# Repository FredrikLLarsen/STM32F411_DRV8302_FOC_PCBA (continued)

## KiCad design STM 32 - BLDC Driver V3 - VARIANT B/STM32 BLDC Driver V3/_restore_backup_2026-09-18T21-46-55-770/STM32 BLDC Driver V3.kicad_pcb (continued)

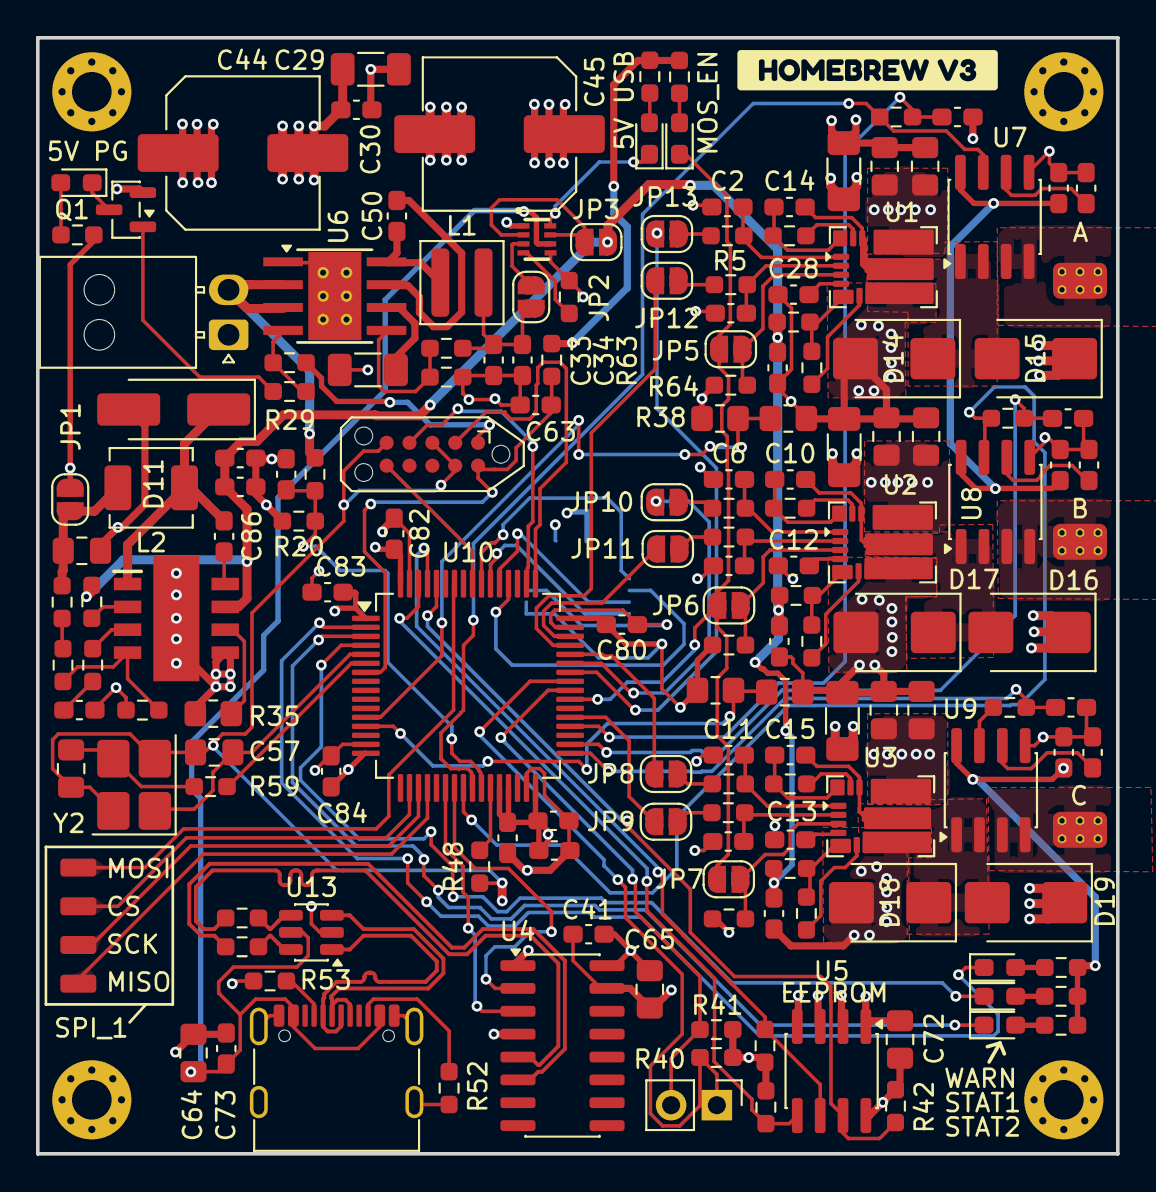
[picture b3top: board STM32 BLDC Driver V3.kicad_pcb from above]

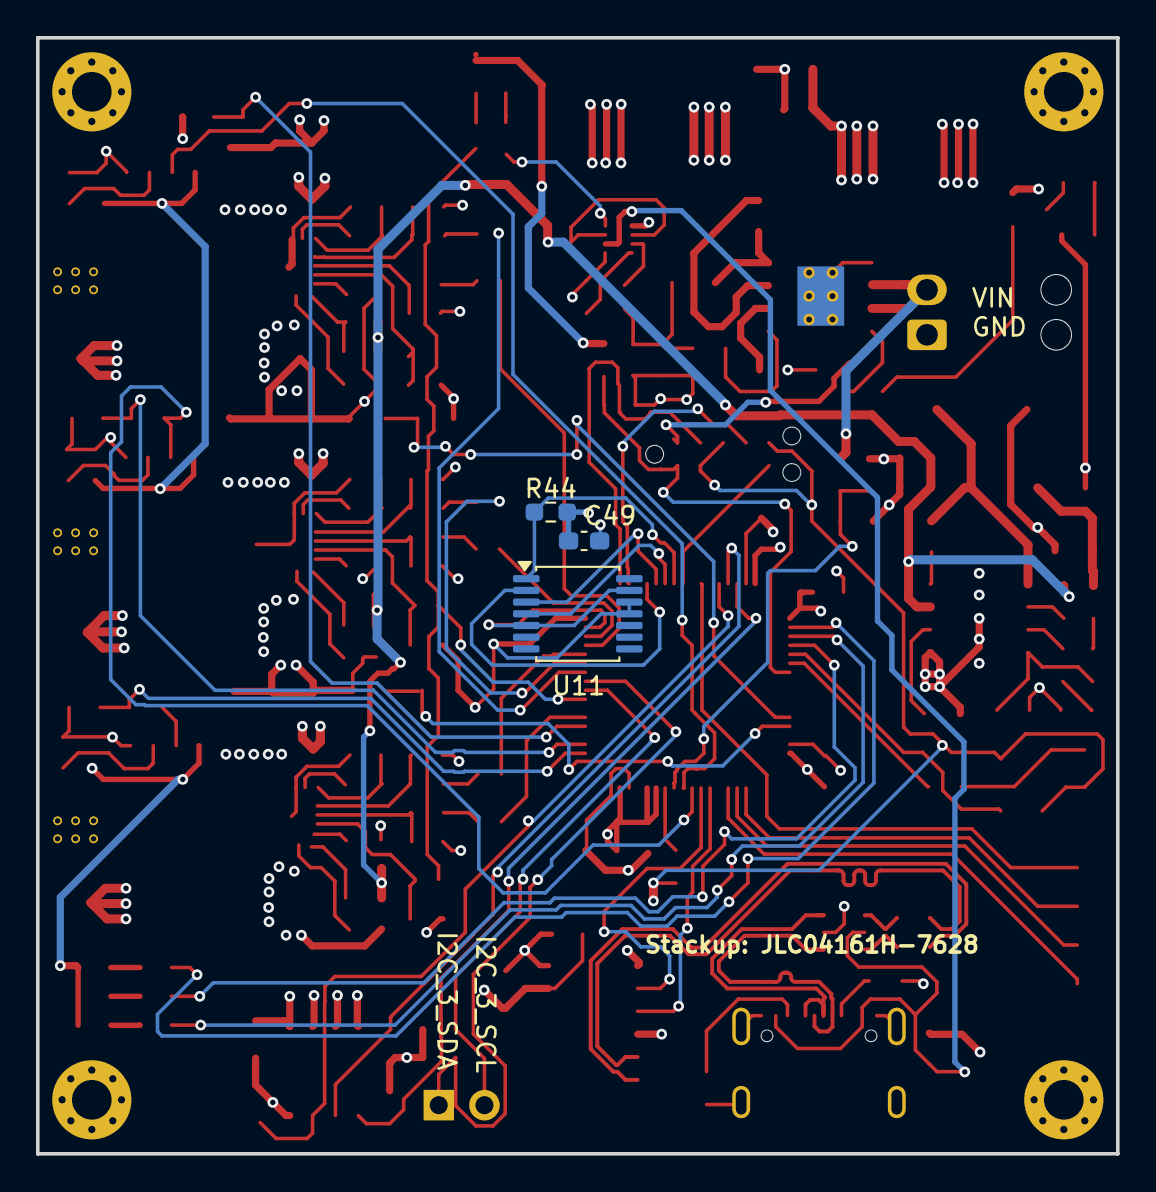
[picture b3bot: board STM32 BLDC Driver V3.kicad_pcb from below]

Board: 4 copper layers, 60.0 x 62.0 mm, 180 parts (3 on the bottom side), 122 nets.

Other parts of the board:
kobee-studio-6AB1898F: Kobee Studio; kobee-studio-6AB1898F

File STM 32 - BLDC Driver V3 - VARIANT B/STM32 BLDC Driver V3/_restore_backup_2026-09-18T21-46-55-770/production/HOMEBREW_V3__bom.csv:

Designator,Footprint,Quantity,Value,LCSC Part #
"C10, C12, C13, C14, C15, C25, C26, C28, C32, C37",0603,10,2.2uF (C57895),
"C11, C2, C5, C6, C7, C9",0603,6,22pF (C7419421),
"C19, C22, C31, C38",1206,4,1uf 100V (C13832),
C27,0603,1,22nF (C696861),
C29,1206,1,4.7uF 100V (C22367839),
C30,0603,1,220nF 100V (C7300906),
"C33, C34",0603,2,22uF 10V (C86295),
"C35, C36, C41",0603,3,10uF 10V (C5137565),
C39,0805,1,47uF 10V (C124129),
"C43, C47, C48, C49, C50",0603,5,0.1uF (C52711259),
"C44, C45",C_Elec_8x10.2,2,100uF 63V (C7471891),
"C57, C58",0805,2,10pF (C520053),
"C62, C63, C80, C82, C83, C84, C85, C86",0603,8,100nF 50V (C1591),
"C64, C65, C72",0805,3,100nF 50V (C28233),
"C66, C67, C68, C69, C70, C71",0805,6,100nF 100V X7R,
C73,0603,1,4.7uF 16V (C7432772),
"C74, C75, C76, C77, C78, C79, C81",0603,7,1nF (C374073),
"D10, D12, D13, D7, D8, D9",0603,6,C5342734,
D11,D_SMA_Handsoldering,1,B340A,
"D14, D15, D16, D17, D18, D19",D_SMB,6,C28646299,
IC1,SOIC127P600X170-9N,1,MP1584EN-LF-Z,
IC2,SOT8,1,LM66200DRLR,
J1,PinHeader_1x02_P2.54mm_Vertical,1,Conn_01x02_Pin,
"J11, J5, J7, J8",STICHED SOLDER PAD_SMALL,4,Conn_01x01_Pin,
J12,USB_C_Receptacle_G-Switch_GT-USB-7010ASV,1,G-Switch GT-USB-7010ASV,
"J2, J3, J4",STICHED SOLDER PAD,3,Conn_01x01_Pin,
J9,Molex_Nano-Fit_105313-xx02_1x02_P2.50mm_Horizontal,1,Conn_01x02_Pin,
"JP1, JP10, JP11, JP12, JP13, JP2, JP3, JP5, JP6, JP7, JP8, JP9",SolderJumper-2_P1.3mm_Open_RoundedPad1.0x1.5mm,12,Jumper_2_Small_Open,
L1,L_Abracon_ASPIAIG-F4020,1,10 µH (C54620135),
L2,L_Sunlord_MWSA0402S,1,22uH (C41438718),
Q1,SOT-23,1,BC847,
"R13, R14, R16, R17, R18, R19",0603,6,10R 0.1W (C109318),
"R2, R4, R5, R6, R7, R8",0603,6,2.2R (C2907006),
R20,0603,1,4.3k 1% (C54920924),
"R21, R23, R40, R41, R42, R44, R51, R57, R58",0603,9,4k7 100mW (C2907034),
"R22, R24, R25, R28, R30, R39, R45",0603,7,820R (C137608),
"R26, R29, R32, R34, R43",0603,5,100k 1% (C2906980),
R27,0603,1,24.9k 1% (C2930080),
R33,0603,1,68k (C2907063),
R35,0805,1,250k (C2501409),
R36,0603,1,22k (C2907015),
"R37, R38",0805,2,8.2k (C17828),
"R46, R47",0603,2,22R (C23345),
"R48, R59, R60, R62, R68",0603,5,0R (C2906974),
"R52, R53",0603,2,5.1k (C2907044),
"R55, R63, R64, R65, R66, R67",0603,6,10k 100mW (C98220),
"TH2, TH3",0805,2,CMFB103F3950FANT (C51597),
"U1, U2, U3",EPC_QFN-13-3EP_3.5x5mm_P0.5mm,3,EPC23104,
U10,LQFP-64_10x10mm_P0.5mm,1,STM32G431RBTx,
U11,TSSOP-14_4.4x5mm_P0.65mm,1,AS5047D,
U13,SOT-23-6,1,USBLC6-2SC6,
U4,SOIC-16_3.9x9.9mm_P1.27mm,1,CH340C,
U5,SOIC-8_3.9x4.9mm_P1.27mm,1,24LC256,
U6,Texas_HTSOP-8-1EP_3.9x4.9mm_P1.27mm_EP2.95x4.9mm_Mask2.4x3.1mm_ThermalVias,1,LMR36520ADDA,
"U7, U8, U9",SOIC-8_3.9x4.9mm_P1.27mm,3,ACS725xLCTR-20AB,
Y2,Crystal_SMD_3225-4Pin_3.2x2.5mm_HandSoldering,1,Crystal_GND24 (C5444547),

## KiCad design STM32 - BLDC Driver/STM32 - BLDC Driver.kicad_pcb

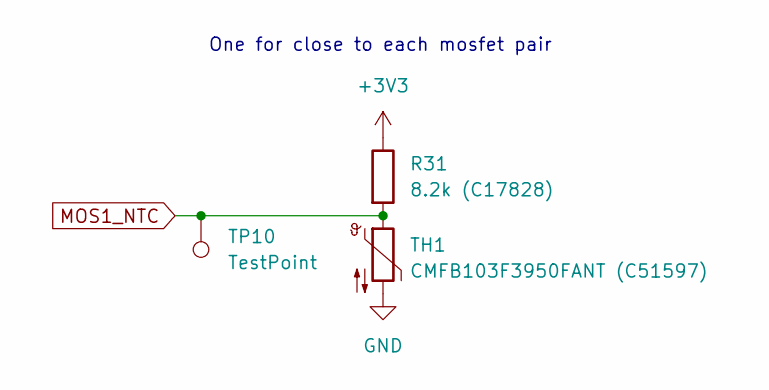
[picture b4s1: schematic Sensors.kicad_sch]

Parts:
R31: 8.2k (C17828); R_0805_2012Metric_Pad1.20x1.40mm_HandSolder
TH1: CMFB103F3950FANT (C51597); R_0805_2012Metric_Pad1.20x1.40mm_HandSolder
TP10: TestPoint; TestPoint_Pad_D3.0mm

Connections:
+3V3: R31.1; also elsewhere on the board
GND: TH1.2; also elsewhere on the board
MOS1_NTC: R31.2, TH1.1, TP10.1; also elsewhere on the board

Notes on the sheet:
One for close to each mosfet pair

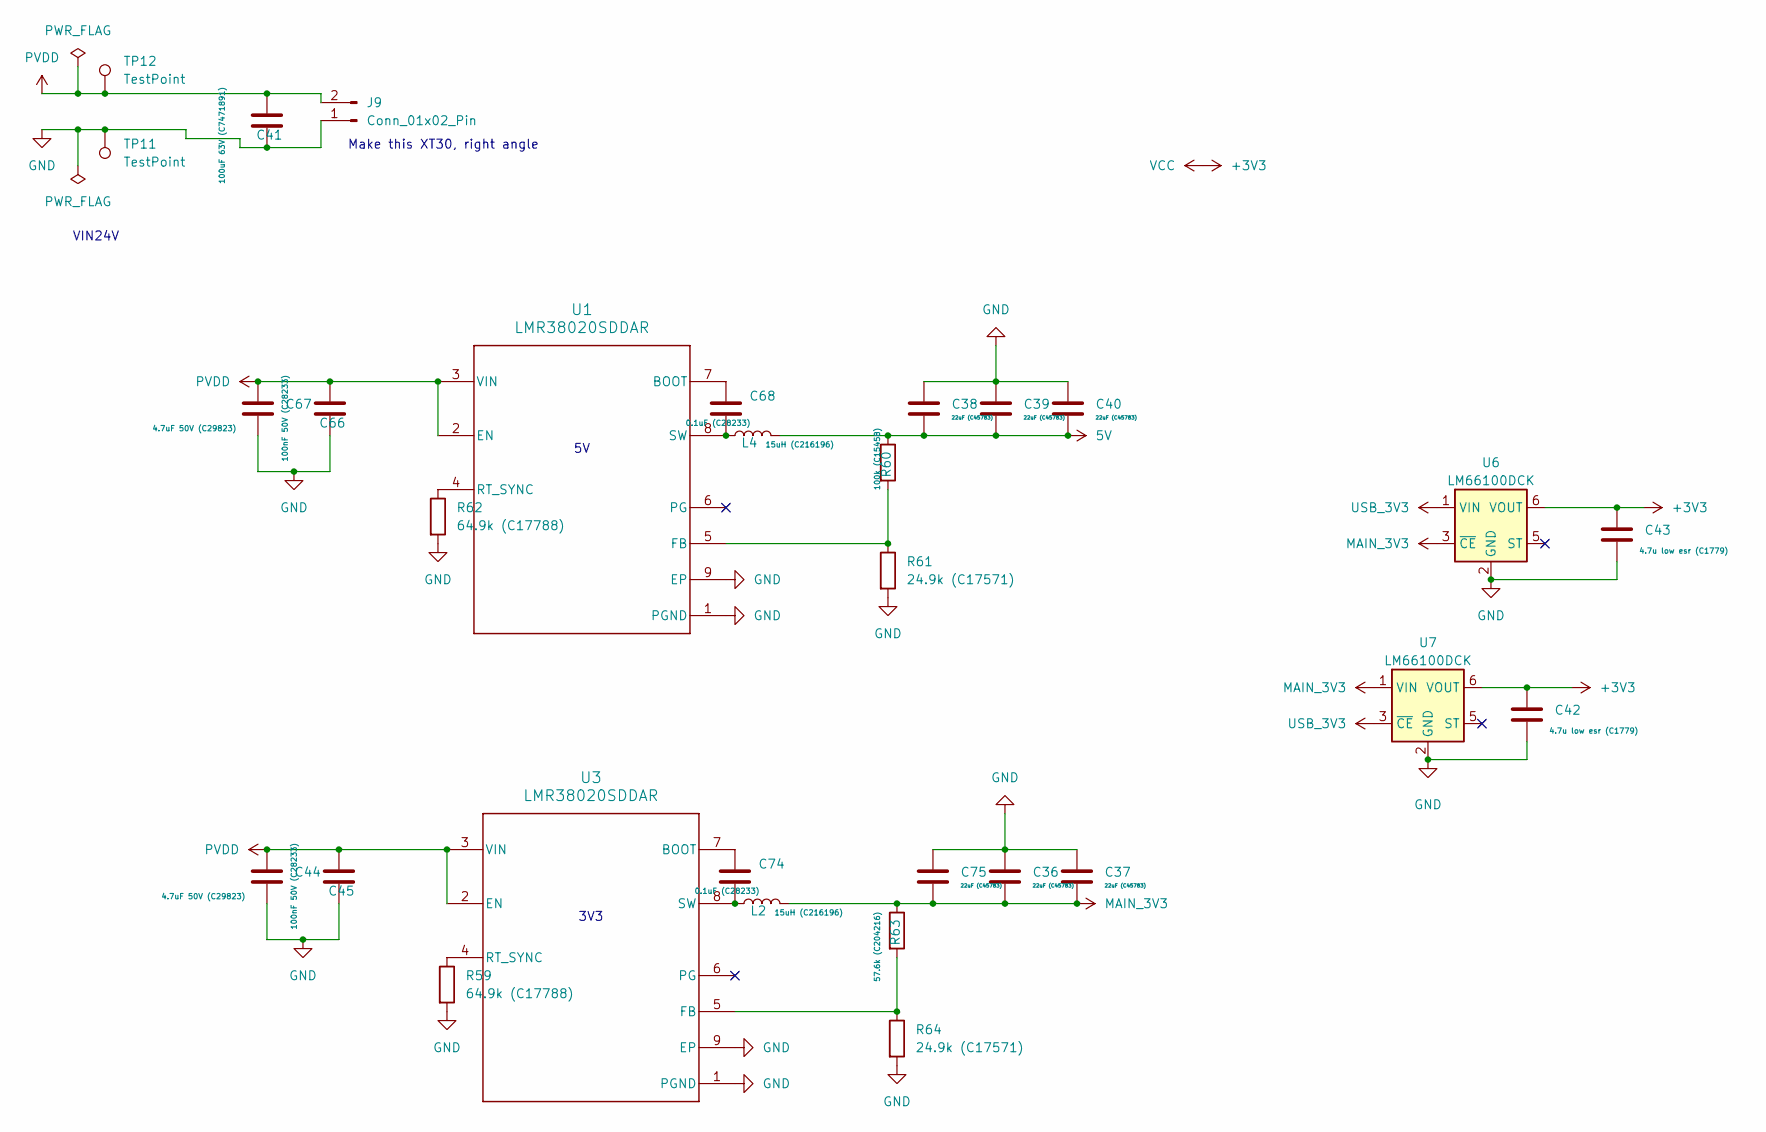
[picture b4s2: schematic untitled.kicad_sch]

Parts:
C36, C37, C38, C39, C40, C75: 22uF (C45783); C_0805_2012Metric_Pad1.18x1.45mm_HandSolder
C41: 100uF 63V (C7471891); C_Elec_8x10.2
C42, C43: 4.7u low esr (C1779); C_0805_2012Metric_Pad1.18x1.45mm_HandSolder
C44, C67: 4.7uF 50V (C29823); C_1206_3216Metric_Pad1.33x1.80mm_HandSolder
C45, C66: 100nF 50V (C28233); C_0805_2012Metric_Pad1.18x1.45mm_HandSolder
C68, C74: 0.1uF (C28233); C_0805_2012Metric_Pad1.18x1.45mm_HandSolder
J9: Conn_01x02_Pin; AMASS_XT30PW-M_1x02_P2.50mm_Horizontal
L2, L4: 15uH (C216196); L_7.3x7.3_H3.5
R59, R62: 64.9k (C17788); R_0805_2012Metric_Pad1.20x1.40mm_HandSolder
R60: 100k (C15458); R_0603_1608Metric_Pad0.98x0.95mm_HandSolder
R61, R64: 24.9k (C17571); R_0805_2012Metric_Pad1.20x1.40mm_HandSolder
R63: 57.6k (C204216); R_0603_1608Metric_Pad0.98x0.95mm_HandSolder
TP11, TP12: TestPoint; TestPoint_Pad_D4.0mm
U1, U3: LMR38020SDDAR; DDA0008E-IPC_A
U6, U7: LM66100DCK; SOT-363_SC-70-6

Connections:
5V: C38.2, C39.2, C40.2, L4.2, R60.1; also elsewhere on the board
+3V3: C42.1, C43.1, U6.6 (VOUT), U7.6 (VOUT); also elsewhere on the board
GND: C36.1, C37.1, C38.1, C39.1, C40.1, C41.1, C42.2, C43.2, C44.2, C45.1, C66.1, C67.2, C75.1, J9.1, R59.2, R61.2, R62.2, R64.2, TP11.1, U1.1 (PGND), U1.9 (EP), U3.1 (PGND), U3.9 (EP), U6.2 (GND), U7.2 (GND); also elsewhere on the board
MAIN_3V3: C36.2, C37.2, C75.2, L2.2, R63.1, U6.3 (~CE), U7.1 (VIN)
unnamed: C68.1, U1.7 (BOOT)
unnamed: R60.2, R61.1, U1.5 (FB)
unnamed: R62.1, U1.4 (RT_SYNC)
unnamed: C68.2, L4.1, U1.8 (SW)
unnamed: C74.1, U3.7 (BOOT)
unnamed: R63.2, R64.1, U3.5 (FB)
unnamed: R59.1, U3.4 (RT_SYNC)
unnamed: C74.2, L2.1, U3.8 (SW)
PVDD: C41.2, C44.1, C45.2, C66.2, C67.1, J9.2, TP12.1, U1.2 (EN), U1.3 (VIN), U3.2 (EN), U3.3 (VIN); also elsewhere on the board
USB_3V3: U6.1 (VIN), U7.3 (~CE); also elsewhere on the board

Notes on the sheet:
Make this XT30, right angle
3V3
VIN24V

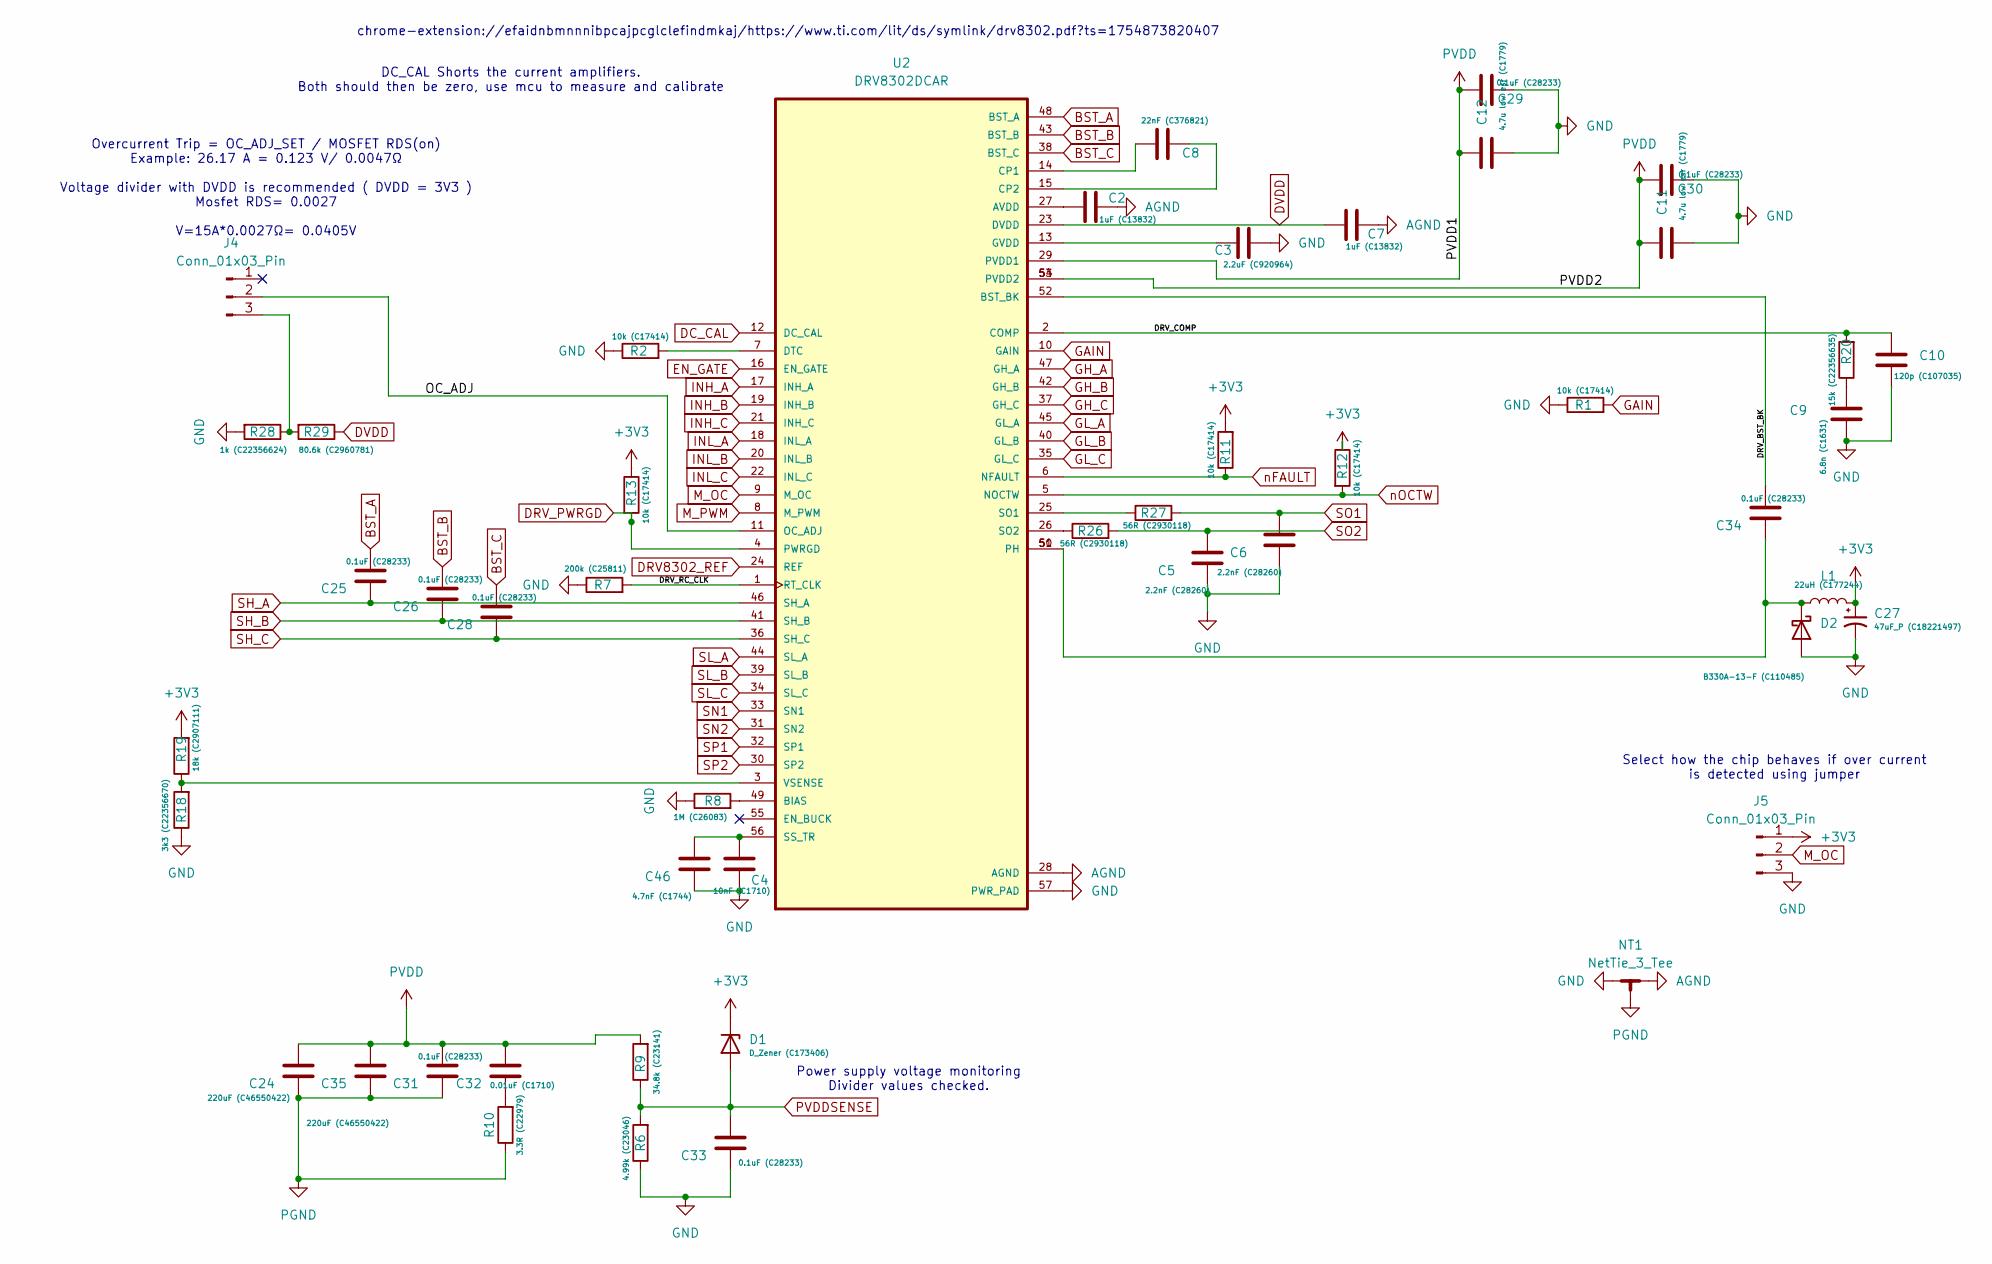
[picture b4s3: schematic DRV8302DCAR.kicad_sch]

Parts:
C2, C7: 1uF (C13832); C_1206_3216Metric_Pad1.33x1.80mm_HandSolder
C3: 2.2uF (C920964); C_1206_3216Metric_Pad1.33x1.80mm_HandSolder
C4: 10nF (C1710); C_0805_2012Metric_Pad1.18x1.45mm_HandSolder
C5, C6: 2.2nF (C28260); C_0805_2012Metric_Pad1.18x1.45mm_HandSolder
C8: 22nF (C376821); C_0603_1608Metric_Pad1.08x0.95mm_HandSolder
C9: 6.8n (C1631); C_0603_1608Metric_Pad1.08x0.95mm_HandSolder
C10: 120p (C107035); C_0603_1608Metric_Pad1.08x0.95mm_HandSolder
C11, C12: 4.7u low esr (C1779); C_0805_2012Metric_Pad1.18x1.45mm_HandSolder
C24, C35: 220uF (C46550422); C_Elec_10x10.2
C25, C26, C28, C29, C30, C31, C33, C34: 0.1uF (C28233); C_0805_2012Metric_Pad1.18x1.45mm_HandSolder
C27: 47uF_P (C18221497); CP_Elec_5x5.4
C32: 0.01uF (C1710); C_0805_2012Metric_Pad1.18x1.45mm_HandSolder
C46: 4.7nF (C1744); C_0805_2012Metric_Pad1.18x1.45mm_HandSolder
D1: D_Zener (C173406); D_SOD-123
D2: B330A-13-F (C110485); D_SMA-SMB_Universal_Handsoldering
J4, J5: Conn_01x03_Pin; PinHeader_1x03_P2.54mm_Vertical
L1: 22uH (C177244); L_Changjiang_FXL0630
NT1: NetTie_3_Tee; NetTie-3_SMD_Pad2.0mm
R1, R2, R11, R12, R13: 10k (C17414); R_0805_2012Metric_Pad1.20x1.40mm_HandSolder
R6: 4.99k (C23046); R_0603_1608Metric_Pad0.98x0.95mm_HandSolder
R7: 200k (C25811); R_0603_1608Metric_Pad0.98x0.95mm_HandSolder
R8: 1M (C26083); R_0402_1005Metric_Pad0.72x0.64mm_HandSolder
R9: 34.8k (C23141); R_0603_1608Metric_Pad0.98x0.95mm_HandSolder
R10: 3.3R (C22979); R_0603_1608Metric_Pad0.98x0.95mm_HandSolder
R18: 3k3 (C22356670); R_0603_1608Metric_Pad0.98x0.95mm_HandSolder
R19: 18k (C2907111); R_0603_1608Metric_Pad0.98x0.95mm_HandSolder
R20: 15k (C22356635); R_0603_1608Metric_Pad0.98x0.95mm_HandSolder
R26, R27: 56R (C2930118); R_0603_1608Metric_Pad0.98x0.95mm_HandSolder
R28: 1k (C22356624); R_0603_1608Metric_Pad0.98x0.95mm_HandSolder
R29: 80.6k (C2960781); R_0805_2012Metric_Pad1.20x1.40mm_HandSolder
U2: DRV8302DCAR; SOP50P810X120-57N

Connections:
+3V3: C27.1, D1.1 (K), J5.1, L1.2, R11.2, R12.1, R13.1, R19.2; also elsewhere on the board
/DRV8302DCAR/DRV_BST_BK: C34.2, U2.52 (BST_BK)
/DRV8302DCAR/DRV_COMP: C10.1, R20.2, U2.2 (COMP)
/DRV8302DCAR/DRV_RC_CLK: R7.2, U2.1 (RT_CLK)
/DRV8302DCAR/OC_ADJ: J4.2, U2.11 (OC_ADJ)
AGND: C2.1, C7.1, NT1.2, U2.28 (AGND)
BST_A: C25.2, U2.48 (BST_A)
BST_B: C26.2, U2.43 (BST_B)
BST_C: C28.2, U2.38 (BST_C)
DC_CAL: U2.12 (DC_CAL); also elsewhere on the board
DRV8302_REF: U2.24 (REF); also elsewhere on the board
DRV_PWRGD: R13.2, U2.4 (PWRGD)
DVDD: C7.2, R29.1, U2.23 (DVDD)
EN_GATE: U2.16 (EN_GATE); also elsewhere on the board
GAIN: R1.2, U2.10 (GAIN)
GH_A: U2.47 (GH_A); also elsewhere on the board
GH_B: U2.42 (GH_B); also elsewhere on the board
GH_C: U2.37 (GH_C); also elsewhere on the board
GL_A: U2.45 (GL_A); also elsewhere on the board
GL_B: U2.40 (GL_B); also elsewhere on the board
GL_C: U2.35 (GL_C); also elsewhere on the board
GND: C3.1, C4.1, C5.1, C6.1, C9.2, C10.2, C11.2, C12.2, C27.2, C29.1, C30.1, C33.1, C46.1, D2.2 (A), J5.3, NT1.1, R1.1, R2.1, R6.1, R7.1, R8.1, R18.1, R28.2, U2.57 (PWR_PAD); also elsewhere on the board
INH_A: U2.17 (INH_A); also elsewhere on the board
INH_B: U2.19 (INH_B); also elsewhere on the board
INH_C: U2.21 (INH_C); also elsewhere on the board
INL_A: U2.18 (INL_A); also elsewhere on the board
INL_B: U2.20 (INL_B); also elsewhere on the board
INL_C: U2.22 (INL_C); also elsewhere on the board
M_OC: J5.2, U2.9 (M_OC)
M_PWM: U2.8 (M_PWM); also elsewhere on the board
unnamed: C9.1, R20.1
unnamed: C32.1, R10.2
unnamed: C34.1, D2.1 (K), L1.1, U2.50 (PH), U2.51 (PH)
unnamed: J4.3, R28.1, R29.2
unnamed: C2.2, U2.27 (AVDD)
unnamed: R8.2, U2.49 (BIAS)
unnamed: C8.2, U2.14 (CP1)
unnamed: C8.1, U2.15 (CP2)
unnamed: R2.2, U2.7 (DTC)
unnamed: C3.2, U2.13 (GVDD)
unnamed: R27.1, U2.25 (SO1)
unnamed: R26.1, U2.26 (SO2)
unnamed: C4.2, C46.2, U2.56 (SS_TR)
unnamed: R18.2, R19.1, U2.3 (VSENSE)
PGND: C24.1, C31.1, C35.1, NT1.3, R10.1; also elsewhere on the board
PVDD: C11.1, C12.1, C24.2, C29.2, C30.2, C31.2, C32.2, C35.2, R9.2, U2.29 (PVDD1), U2.53 (PVDD2), U2.54 (PVDD2); also elsewhere on the board
PVDDSENSE: C33.2, D1.2 (A), R6.2, R9.1; also elsewhere on the board
SH_A: C25.1, U2.46 (SH_A); also elsewhere on the board
SH_B: C26.1, U2.41 (SH_B); also elsewhere on the board
SH_C: C28.1, U2.36 (SH_C); also elsewhere on the board
SL_A: U2.44 (SL_A); also elsewhere on the board
SL_B: U2.39 (SL_B); also elsewhere on the board
SL_C: U2.34 (SL_C); also elsewhere on the board
SN1: U2.33 (SN1); also elsewhere on the board
SN2: U2.31 (SN2); also elsewhere on the board
SO1: C6.2, R27.2
SO2: C5.2, R26.2
SP1: U2.32 (SP1); also elsewhere on the board
SP2: U2.30 (SP2); also elsewhere on the board
nFAULT: R11.1, U2.6 (NFAULT); also elsewhere on the board
nOCTW: R12.2, U2.5 (NOCTW); also elsewhere on the board

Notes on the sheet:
Power supply voltage monitoring Divider values checked.
DC_CAL Shorts the current amplifiers. Both should then be zero, use mcu to measure and calibrate
Select how the chip behaves if over current is detected using jumper
chrome-extension://efaidnbmnnnibpcajpcglclefindmkaj/https://www.ti.com/lit/ds/symlink/drv8302.pdf?ts=1754873820407
Overcurrent Trip = OC_ADJ_SET / MOSFET RDS(on) Example: 26.17 A = 0.123 V/ 0.0047Ω Voltage divider with DVDD is recommended ( DVDD = 3V3 ) Mosfet RDS= 0.0027 V=15A*0.0027Ω= 0.0405V

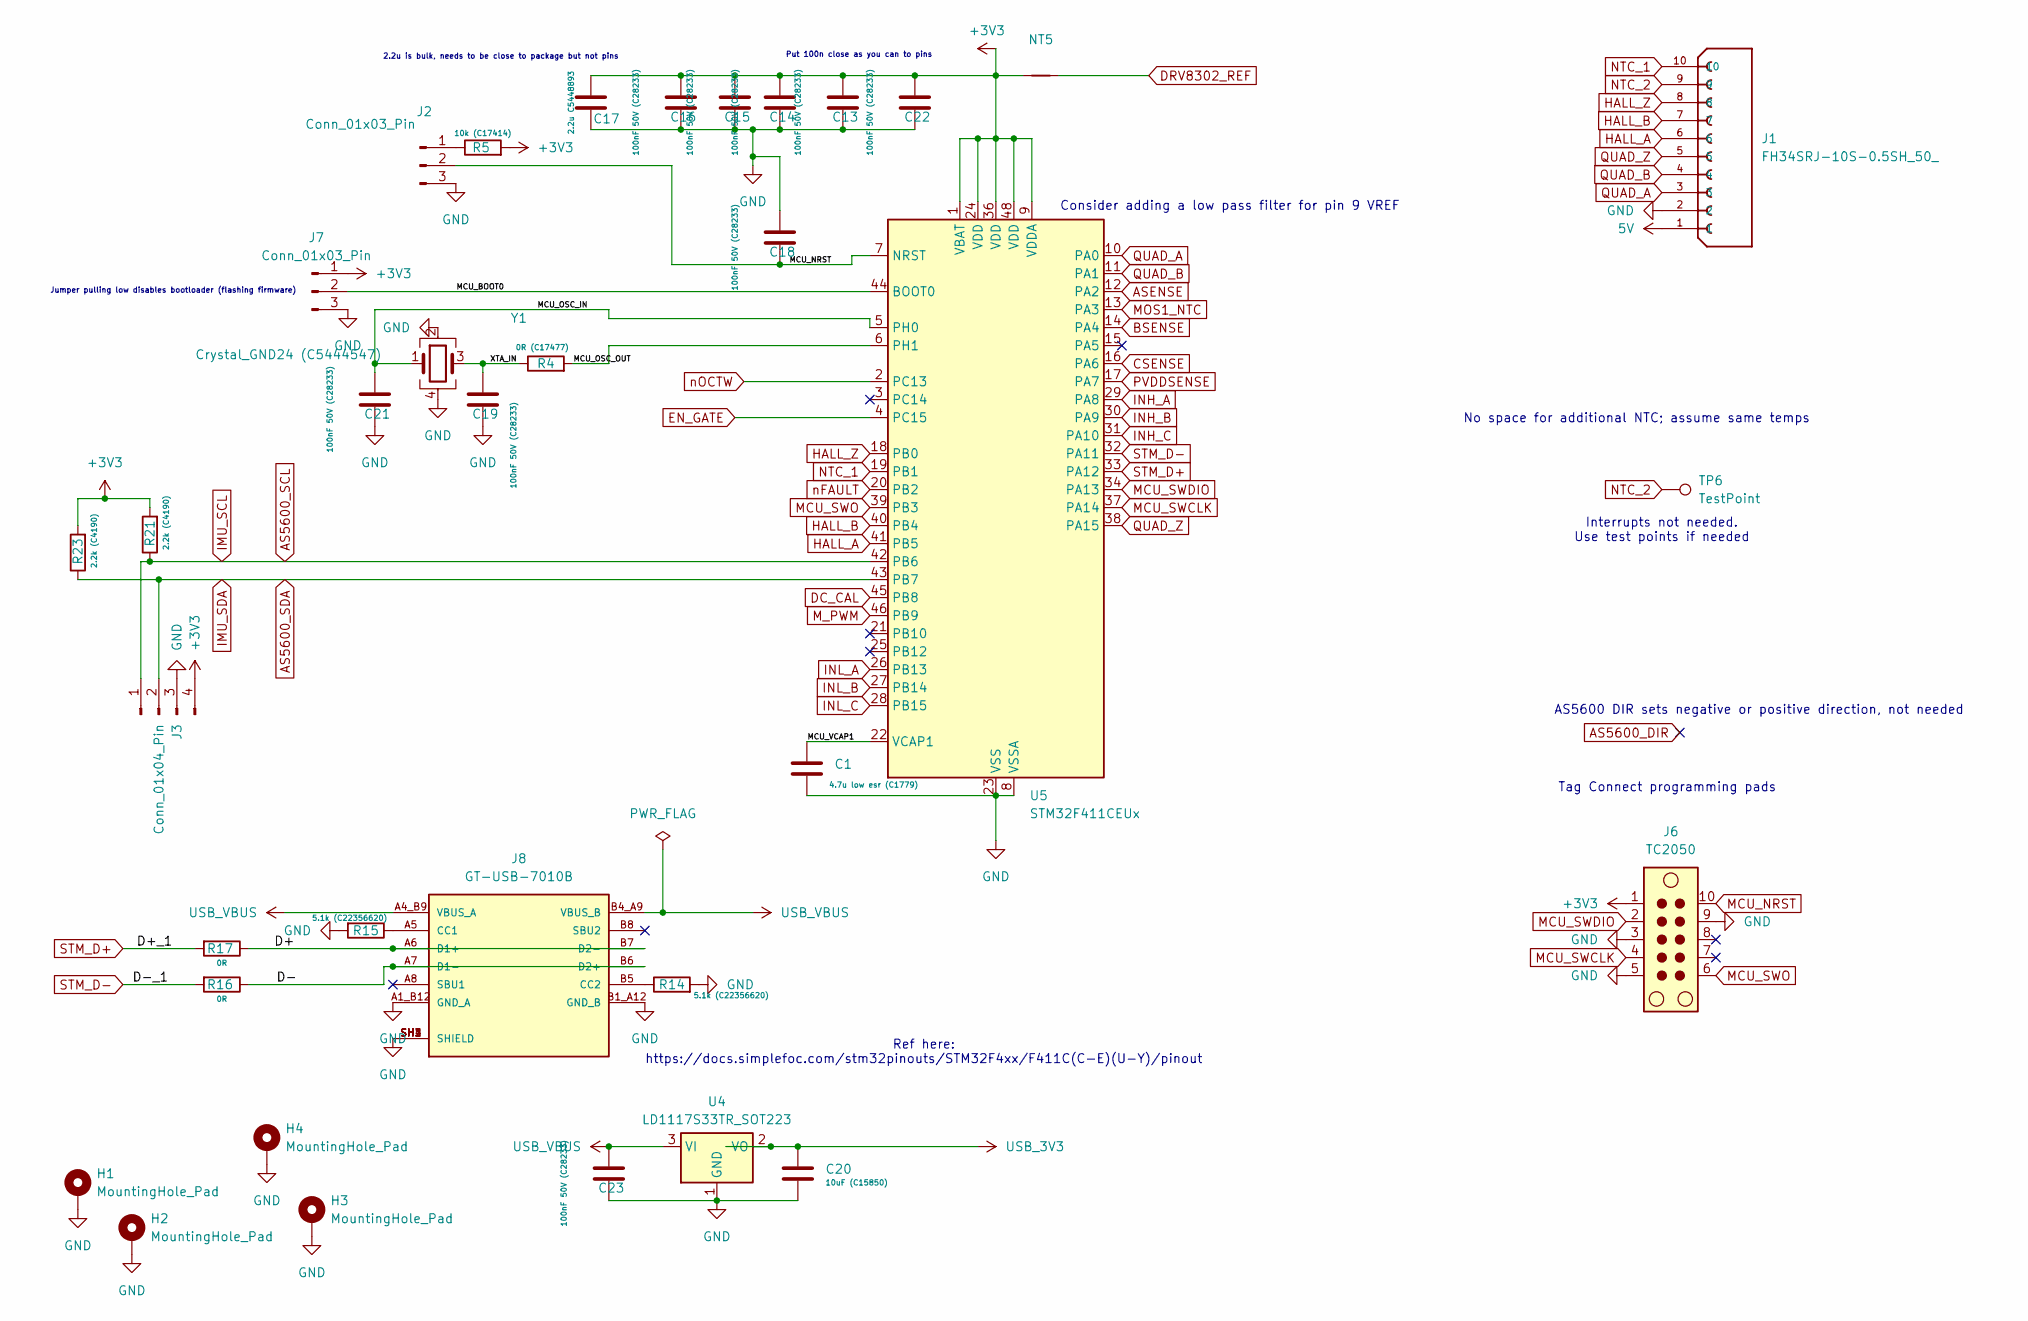
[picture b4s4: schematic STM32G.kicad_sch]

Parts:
C1: 4.7u low esr (C1779); C_0805_2012Metric_Pad1.18x1.45mm_HandSolder
C13, C14, C15, C16, C18, C19, C21, C22, C23: 100nF 50V (C28233); C_0805_2012Metric_Pad1.18x1.45mm_HandSolder
C17: 2.2u C5448893; C_0805_2012Metric_Pad1.18x1.45mm_HandSolder
C20: 10uF (C15850); C_0805_2012Metric_Pad1.18x1.45mm_HandSolder
H1, H2, H3, H4: MountingHole_Pad; MountingHole_3.2mm_M3_Pad_Via
J1: FH34SRJ-10S-0.5SH_50_; HRS_FH34SRJ-10S-0.5SH_50_; PARTREV Apr.1.2022
J2, J7: Conn_01x03_Pin; PinHeader_1x03_P2.54mm_Vertical
J3: Conn_01x04_Pin; PinHeader_1x04_P2.54mm_Vertical
J6: TC2050; Tag-Connect_TC2050-IDC-NL_2x05_P1.27mm_Vertical
J8: GT-USB-7010B; G-SWITCH_GT-USB-7010B; PARTREV A0
NT5: NetTie_2; NetTie-2_SMD_Pad0.5mm
R4: 0R (C17477); R_0805_2012Metric_Pad1.20x1.40mm_HandSolder
R5: 10k (C17414); R_0805_2012Metric_Pad1.20x1.40mm_HandSolder
R14, R15: 5.1k (C22356620); R_0603_1608Metric_Pad0.98x0.95mm_HandSolder
R16, R17: 0R; R_0603_1608Metric_Pad0.98x0.95mm_HandSolder
R21, R23: 2.2k (C4190); R_0603_1608Metric_Pad0.98x0.95mm_HandSolder
TP6: TestPoint; TestPoint_Pad_D4.0mm
U4: LD1117S33TR_SOT223; SOT-223-3_TabPin2
U5: STM32F411CEUx; QFN-48-1EP_7x7mm_P0.5mm_EP5.6x5.6mm
Y1: Crystal_GND24 (C5444547); Crystal_SMD_3225-4Pin_3.2x2.5mm_HandSoldering

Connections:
5V: J1.1; also elsewhere on the board
+3V3: C13.2, C14.2, C15.2, C16.2, C17.1, C22.2, J3.4, J6.1, J7.1, NT5.1, R5.2, R21.2, R23.2, U5.1 (VBAT), U5.9 (VDDA), U5.24 (VDD), U5.36 (VDD), U5.48 (VDD); also elsewhere on the board
/STM32G/D+: J8.A6 (D1+), J8.B7 (D2-), R17.1
/STM32G/D-: J8.A7 (D1-), J8.B6 (D2+), R16.1
/STM32G/MCU_BOOT0: J7.2, U5.44 (BOOT0)
/STM32G/MCU_OSC_IN: C21.2, U5.5 (PH0), Y1.1
/STM32G/MCU_OSC_OUT: R4.2, U5.6 (PH1)
/STM32G/MCU_VCAP1: C1.1, U5.22 (VCAP1)
/STM32G/XTA_IN: C19.2, R4.1, Y1.3
AS5600_SCL: J3.1, R21.1, U5.42 (PB6)
AS5600_SDA: J3.2, R23.1, U5.43 (PB7)
ASENSE: U5.12 (PA2); also elsewhere on the board
BSENSE: U5.14 (PA4); also elsewhere on the board
CSENSE: U5.16 (PA6); also elsewhere on the board
DC_CAL: U5.45 (PB8); also elsewhere on the board
DRV8302_REF: NT5.2; also elsewhere on the board
EN_GATE: U5.4 (PC15); also elsewhere on the board
GND: C1.2, C13.1, C14.1, C15.1, C16.1, C17.2, C18.2, C19.1, C20.2, C21.1, C22.1, C23.1, H1.1, H2.1, H3.1, H4.1, J1.2, J2.3, J3.3, J6.3, J6.5, J6.9, J7.3, J8.A1_B12 (GND_A), J8.B1_A12 (GND_B), J8.SH1 (SHIELD), J8.SH2 (SHIELD), J8.SH3 (SHIELD), J8.SH4 (SHIELD), R14.2, R15.2, U4.1 (GND), U5.8 (VSSA), U5.23 (VSS), U5.35 (VSS), U5.47 (VSS), U5.49 (VSS), Y1.2, Y1.4; also elsewhere on the board
HALL_A: J1.6, U5.41 (PB5)
HALL_B: J1.7, U5.40 (PB4)
HALL_Z: J1.8, U5.18 (PB0)
INH_A: U5.29 (PA8); also elsewhere on the board
INH_B: U5.30 (PA9); also elsewhere on the board
INH_C: U5.31 (PA10); also elsewhere on the board
INL_A: U5.26 (PB13); also elsewhere on the board
INL_B: U5.27 (PB14); also elsewhere on the board
INL_C: U5.28 (PB15); also elsewhere on the board
MCU_NRST: C18.1, J2.2, J6.10, U5.7 (NRST)
MCU_SWCLK: J6.4, U5.37 (PA14)
MCU_SWDIO: J6.2, U5.34 (PA13)
MCU_SWO: J6.6, U5.39 (PB3)
MOS1_NTC: U5.13 (PA3); also elsewhere on the board
M_PWM: U5.46 (PB9); also elsewhere on the board
NTC_1: J1.10, U5.19 (PB1)
NTC_2: J1.9, TP6.1
unnamed: J2.1, R5.1
unnamed: J8.A5 (CC1), R15.1
unnamed: J8.B5 (CC2), R14.1
PVDDSENSE: U5.17 (PA7); also elsewhere on the board
QUAD_A: J1.3, U5.10 (PA0)
QUAD_B: J1.4, U5.11 (PA1)
QUAD_Z: J1.5, U5.38 (PA15)
STM_D+: R17.2, U5.33 (PA12)
STM_D-: R16.2, U5.32 (PA11)
USB_3V3: C20.1, U4.2 (VO); also elsewhere on the board
USB_VBUS: C23.2, J8.A4_B9 (VBUS_A), J8.B4_A9 (VBUS_B), U4.3 (VI)
nFAULT: U5.20 (PB2); also elsewhere on the board
nOCTW: U5.2 (PC13); also elsewhere on the board

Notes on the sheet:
Jumper pulling low disables bootloader (flashing firmware)
Consider adding a low pass filter for pin 9 VREF
Interrupts not needed. Use test points if needed
Ref here: https://docs.simplefoc.com/stm32pinouts/STM32F4xx/F411C(C-E)(U-Y)/pinout
2.2u is bulk, needs to be close to package but not pins
AS5600 DIR sets negative or positive direction, not needed
No space for additional NTC; assume same temps
Put 100n close as you can to pins
Tag Connect programming pads
